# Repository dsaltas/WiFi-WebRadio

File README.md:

## WiFi WebRadio

This is a hardware project for [Ka-Radio](https://github.com/karawin/Ka-Radio).

It is based on [ESP8266](https://espressif.com/en/products/hardware/esp8266ex/overview) 
chip and audio codec [VS1053b](http://www.vlsi.fi/en/products/vs1053.html) chip.

### Features

- You can power it with 3V3 **or** 5V. Do **NOT** use both power inputs at the same time.

- You can connect an external [keypad](https://github.com/karawin/Ka-Radio/blob/master/Hardware/controles.pdf) for control. Just unsolder the ADC jumper.

- <del>The RXD pin is 5V tolerant so you can connect a 5V microcontroller</del>.
  <br>It's official! ESP8266 I/Os are 5V tolerant.

- Output is line-out with large audio grade electrolytic capacitors. Safe to connect an external amplifier.

- You can use two types of SRAM. 23LCV1024 **or** 23LC1024. Just solder the proper jumper.

Tested and working as expected.

You can order the pcb from [OSH Park](https://oshpark.com/shared_projects/Byku3T3d).

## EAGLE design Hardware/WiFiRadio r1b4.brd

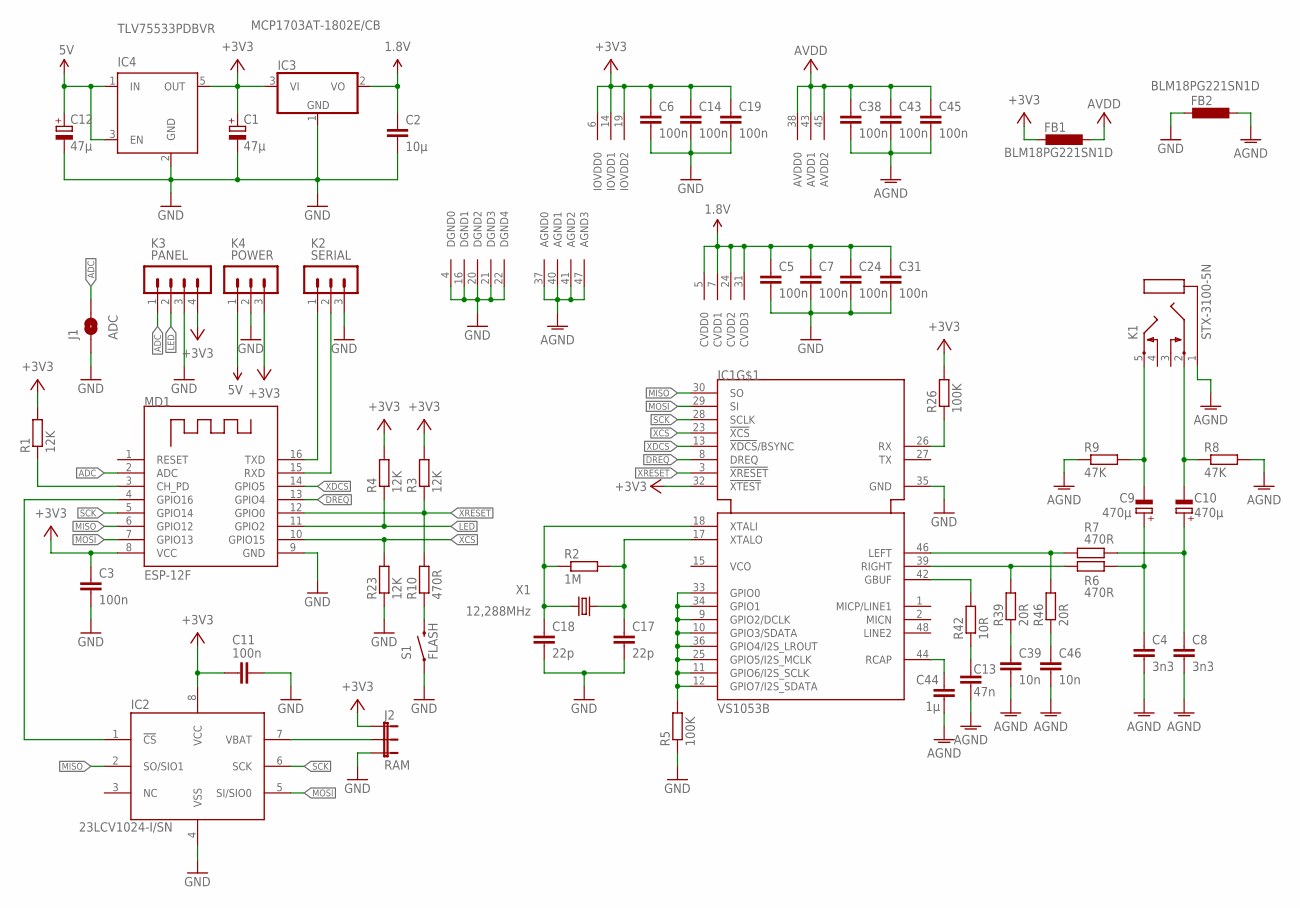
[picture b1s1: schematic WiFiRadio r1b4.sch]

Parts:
C1, C12: 47μ; SMC_B
C2: 10μ; C0805
C3, C5, C6, C7, C11, C14, C19, C24, C31, C38, C43, C45: 100n; C0603
C4, C8: 3n3; C0805
C9, C10: 470μ; E3,5-8
C13: 47n; C0805
C17, C18: 22p; C0805
C39, C46: 10n; C0805
C44: 1μ; C0805
FB1, FB2: BLM18PG221SN1D; L2012C
IC1: VS1053B; LQFP48
IC2: 23LCV1024-I/SN; SO-08
IC3: MCP1703AT-1802E/CB; SOT23
IC4: TLV75533PDBVR; SOT23-5
J1: ADC; SJ_2S
J2: RAM; SJ_3
K1: STX-3100-5N; STX3100
K2: SERIAL; MA03-1
K3: PANEL; MA04-1
K4: POWER; MA03-1
MD1: ESP-12F
R1, R3, R4, R23: 12K; R0805
R2: 1M; R0805
R5, R26: 100K; R0805
R6, R7, R10: 470R; R0805
R8, R9: 47K; R0805
R39, R46: 20R; R0805
R42: 10R; R0805
S1: FLASH; TACTILE-SWITCH-SMD
X1: 12,288MHz; HC49/S

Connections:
1.8V: C2.1, C5.1, C7.1, C24.1, C31.1, IC1.5 (CVDD0), IC1.7 (CVDD1), IC1.24 (CVDD2), IC1.31 (CVDD3), IC3.2 (VO)
5V: C12.+, IC4.1 (IN), IC4.3 (EN), K4.1
+3V3: C1.+, C3.1, C6.1, C11.1, C14.1, C19.1, FB1.2, IC1.6 (IOVDD0), IC1.14 (IOVDD1), IC1.19 (IOVDD2), IC1.32 (!XTEST), IC2.8 (VCC), IC3.3 (VI), IC4.5 (OUT), J2.1, K3.4, K4.3, MD1.8 (VCC), R1.2, R3.2, R4.2, R26.2
ADC: J1.2, K3.1, MD1.2 (ADC)
AGND: C4.2, C8.2, C13.2, C38.2, C39.2, C43.2, C44.2, C45.2, C46.2, FB2.1, IC1.37 (AGND0), IC1.40 (AGND1), IC1.41 (AGND2), IC1.47 (AGND3), K1.1, R8.2, R9.1
DREQ: IC1.8 (DREQ), MD1.13 (GPIO4)
GND: C1.-, C2.2, C3.2, C5.2, C6.2, C7.2, C11.2, C12.-, C14.2, C17.2, C18.2, C19.2, C24.2, C31.2, FB2.2, IC1.4 (DGND0), IC1.16 (DGND1), IC1.20 (DGND2), IC1.21 (DGND3), IC1.22 (DGND4), IC1.35 (GND), IC2.4 (VSS), IC3.1 (GND), IC4.2 (GND), J1.1, J2.3, K2.3, K3.3, K4.2, MD1.9 (GND), R5.1, R23.1, S1.1
GPIO: IC1.9 (GPIO2/DCLK), IC1.10 (GPIO3/SDATA), IC1.11 (GPIO6/I2S_SCLK), IC1.12 (GPIO7/I2S_SDATA), IC1.25 (GPIO5/I2S_MCLK), IC1.33 (GPIO0), IC1.34 (GPIO1), IC1.36 (GPIO4/I2S_LROUT), R5.2
LED: K3.2, MD1.11 (GPIO2), R4.1
LEFT: IC1.46 (LEFT), R7.1, R46.2
MISO: IC1.30 (SO), IC2.2 (SO/SIO1), MD1.6 (GPIO12)
MOSI: IC1.29 (SI), IC2.5 (SI/SIO0), MD1.7 (GPIO13)
unnamed: IC2.1 (!CS), MD1.4 (GPIO16)
unnamed: MD1.3 (CH_PD), R1.1
unnamed: C17.1, IC1.17 (XTALO), R2.2, X1.1
unnamed: C18.1, IC1.18 (XTALI), R2.1, X1.2
unnamed: IC1.42 (GBUF), R42.2
unnamed: C4.1, C9.+, R6.2
unnamed: C8.1, C10.+, R7.2
unnamed: IC2.7 (VBAT), J2.2
unnamed: C39.1, R39.1
unnamed: C46.1, R46.1
unnamed: C13.1, R42.1
unnamed: C9.-, K1.5, R9.2
unnamed: C10.-, K1.2, R8.1
unnamed: R10.1, S1.3 (2)
RCAP: C44.1, IC1.44 (RCAP)
RIGHT: IC1.39 (RIGHT), R6.1, R39.2
RX: IC1.26 (RX), R26.1
RXD: K2.2, MD1.15 (RXD)
SCK: IC1.28 (SCLK), IC2.6 (SCK), MD1.5 (GPIO14)
TXD: K2.1, MD1.16 (TXD)
V+: C38.1, C43.1, C45.1, FB1.1, IC1.38 (AVDD0), IC1.43 (AVDD1), IC1.45 (AVDD2)
XCS: IC1.23 (!XCS), MD1.10 (GPIO15), R23.2
XDCS: IC1.13 (!XDCS!/BSYNC), MD1.14 (GPIO5)
XRESET: IC1.3 (!XRESET), MD1.12 (GPIO0), R3.1, R10.2

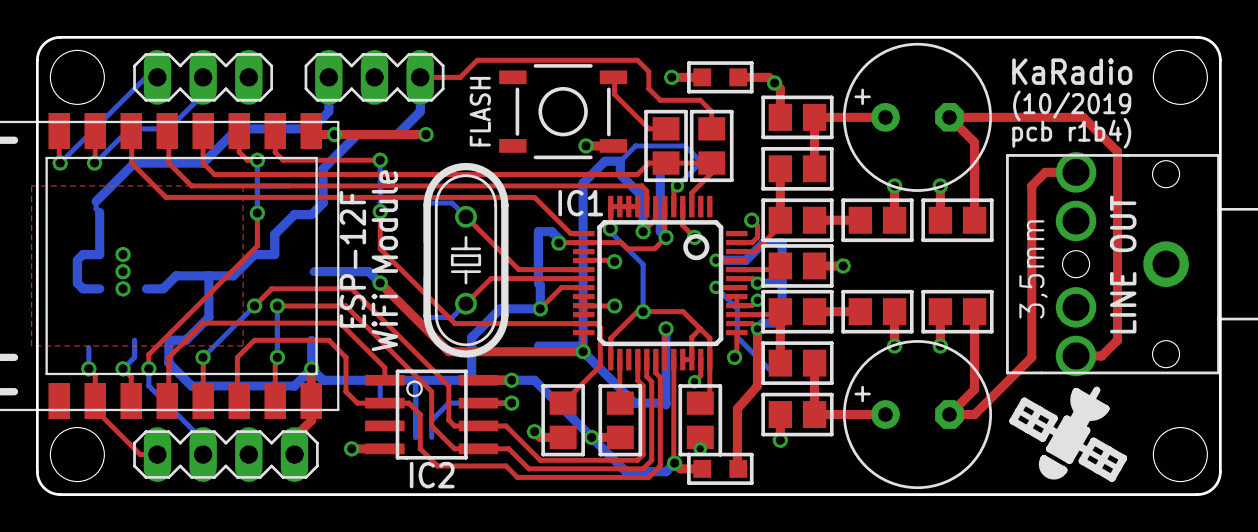
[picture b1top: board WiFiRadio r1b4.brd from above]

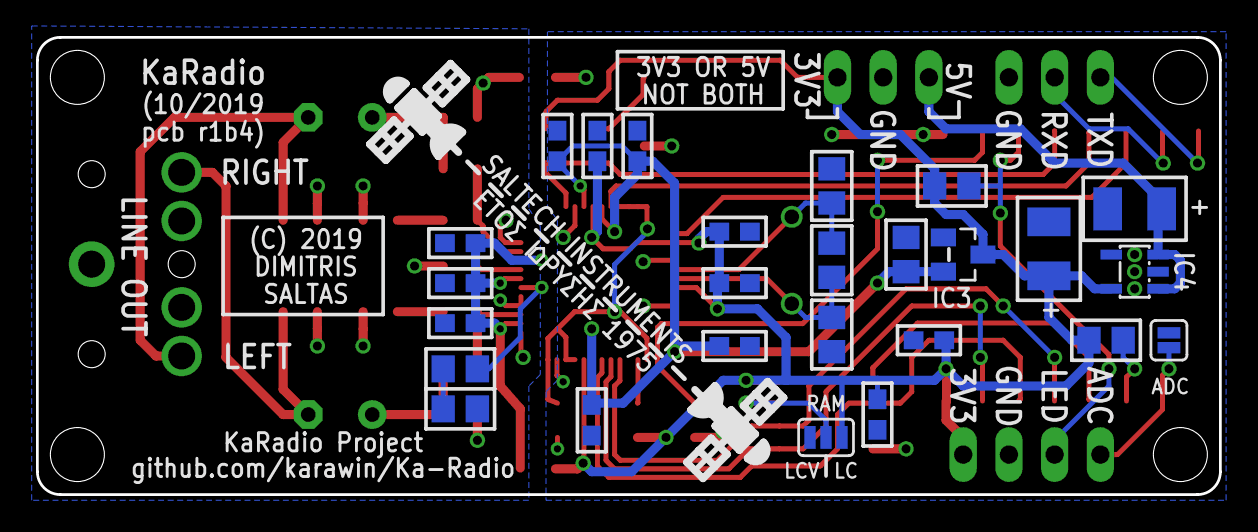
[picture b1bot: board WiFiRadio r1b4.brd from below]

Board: 2 copper layers, 65.7 x 25.4 mm, 55 parts (26 on the bottom side), 36 nets.

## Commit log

2017-03-07 EAGLE Schematic
2017-03-07 EAGLE Board
2017-03-07 Schematic in PDF
2017-03-09 Bill of materials
2017-08-26 Gerber files added.
2018-01-03 Added reference designators.
2019-10-23 Schematics in PDF
2019-10-23 Create test
2020-01-17 Add BOM
2020-01-17 Replace BOM

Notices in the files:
Hardware/WiFiRadio r1b4.brd:
(C) 2019
parts and their libraries:
SparkFun-Electromechanical: Licensing: Creative Commons ShareAlike 4.0 International - https://creativecommons.org/licenses/by-sa/4.0
